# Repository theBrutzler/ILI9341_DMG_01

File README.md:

# ILI9341_DMG_01
 GESP Mainboard for ORIGINAL GAMEBOY

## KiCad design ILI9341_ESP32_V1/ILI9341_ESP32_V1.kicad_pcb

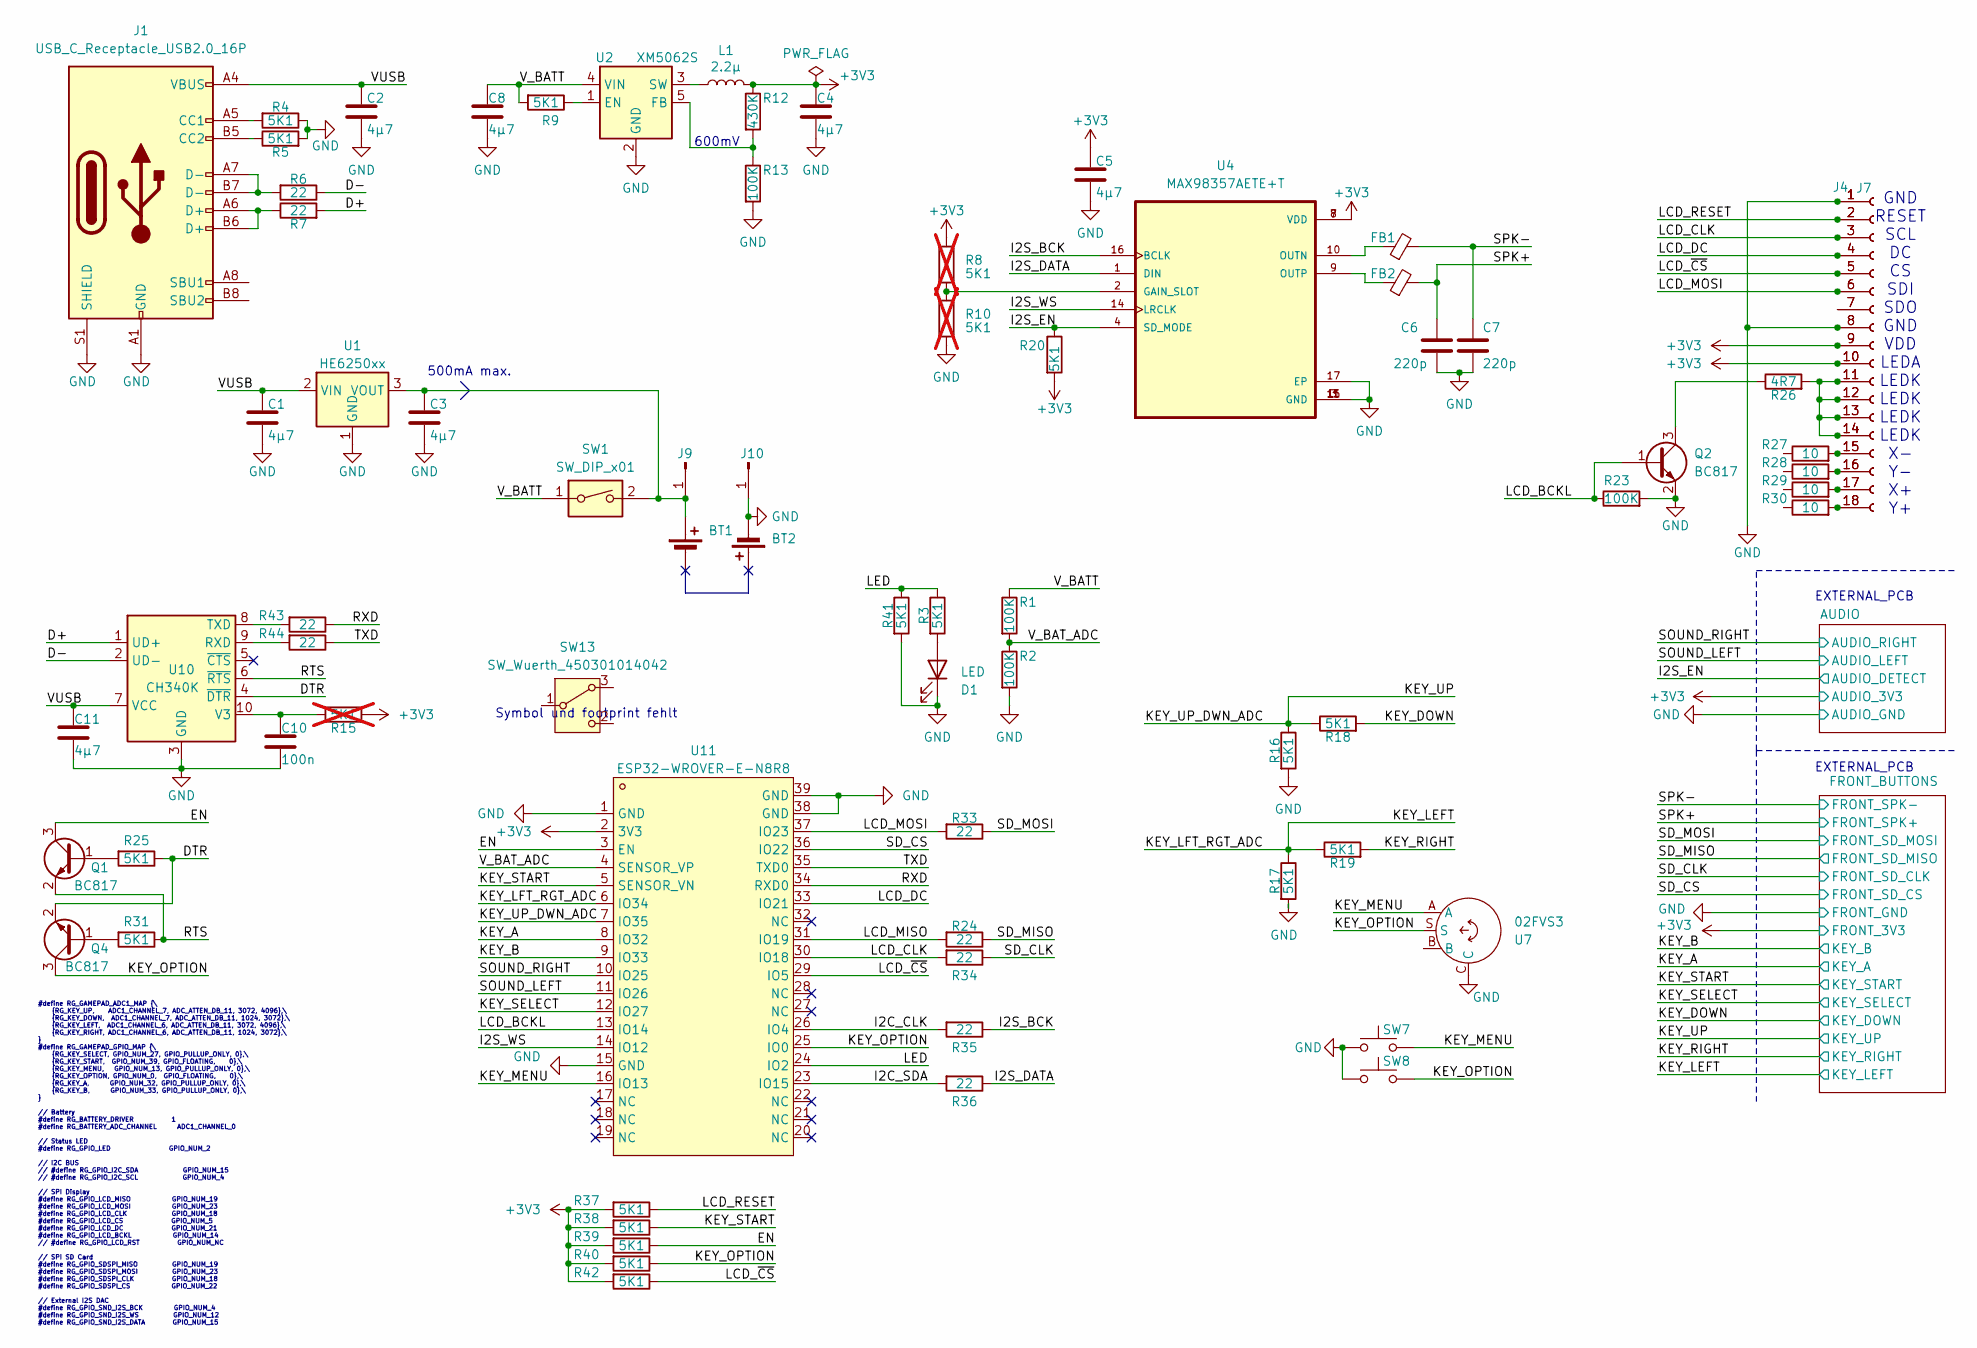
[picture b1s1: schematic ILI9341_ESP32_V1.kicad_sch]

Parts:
BT1: Battery_Cell; BATTERY_AA_SMD_PLUS; LCSC C964874
BT2: Battery_Cell; BATTERY_AA_SMD_MINUS; LCSC C964876
C1, C2, C3, C4, C5, C8, C11: 4µ7; C_1206_3216Metric
C6, C7: 220p; C_0603_1608Metric
C10: 100n; C_1206_3216Metric
D1: LED; LED_0603_1608Metric
FB1, FB2: FerriteBead_Small; L_0805_2012Metric
J1: USB_C_Receptacle_USB2.0_16P; USB_C_Receptacle_HRO_TYPE-C-31-M-12
J4, J7: Conn_01x18_Socket; solder connector 0.8mm 18 pin
J9: Conn_01x01_Pin; NINTENDO_PLUS
J10: Conn_01x01_Pin; NINTENDO_MINUS
L1: 2.2µ; L_1210_3225Metric_Pad1.42x2.65mm_HandSolder
Q1, Q2, Q4: BC817; SOT-23
R1, R2, R13, R23: 100K; R_0603_1608Metric_Pad0.98x0.95mm_HandSolder
R3, R4, R5, R9, R16, R17, R18, R19, R25, R31, R37, R38, R39, R40, R41, R42: 5K1; R_0603_1608Metric_Pad0.98x0.95mm_HandSolder
R6, R7, R24, R33, R34, R35, R36, R43, R44: 22; R_0603_1608Metric_Pad0.98x0.95mm_HandSolder
R8, R10: 5K1; R_0603_1608Metric; LCSC C26000; not fitted
R12: 430K; R_0603_1608Metric_Pad0.98x0.95mm_HandSolder
R15: 5K1; R_0603_1608Metric_Pad0.98x0.95mm_HandSolder; not fitted
R20: 5K1; R_0603_1608Metric; LCSC C26000
R26: 4R7; R_0603_1608Metric_Pad0.98x0.95mm_HandSolder
R27, R28, R29, R30: 10; R_0603_1608Metric_Pad0.98x0.95mm_HandSolder
SW1: SW_DIP_x01; SW_SPDT_PCM12; LCSC C3036445 C223846
SW7, SW8: SW_Push; RubberpadButton_250µ_250µ
SW13: SW_Wuerth_450301014042; SW_Slide-03_Wuerth-WS-SLTV_10x2.5x6.4_P2.54mm; LCSC C2939282
U1: HE6250xx; SOT-89-3; LCSC C711940
U2: XM5062S; SOT-23-5; LCSC C2924930
U4: MAX98357AETE+T; QFN-16-1EP_3x3mm_P0.5mm_EP1.45x1.45mm; LCSC C910544
U7: 02FVS3; LCSC C2925423
U10: CH340K; SSOP-10_3.9x4.9mm_P1.00mm_EP_3mmx2mm; LCSC C968586
U11: ESP32-WROVER-E-N8R8; WIFI-SMD_ESP32-WROVER-IE8MB; LCSC Part C2973667

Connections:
+3V3: C4.1, C5.1, J4.9, J4.10, J7.9, J7.10, L1.2, R8.1, R12.1, R15.2, R20.2, R37.2, R38.2, R39.2, R40.2, R42.2, U4.7 (VDD), U4.8 (VDD), U11.2 (3V3); also elsewhere on the board
/D+: R7.2, U10.1 (UD+)
/D-: R6.1, U10.2 (UD-)
/DTR: Q4.2 (E), R25.1, U10.4 (~DTR)
/EN: Q1.3 (C), R39.1, U11.3 (EN)
/I2C_CLK: R35.2, U11.26 (IO4)
/I2C_SDA: R36.2, U11.23 (IO15)
/I2S_BCK: R35.1, U4.16 (BCLK)
/I2S_DATA: R36.1, U4.1 (DIN)
/I2S_EN: R20.1, U4.4 (SD_MODE); also elsewhere on the board
/I2S_WS: U4.14 (LRCLK), U11.14 (IO12)
/KEY_A: U11.8 (IO32); also elsewhere on the board
/KEY_B: U11.9 (IO33); also elsewhere on the board
/KEY_DOWN: R18.2; also elsewhere on the board
/KEY_LEFT: R17.1, R19.1, U11.6 (IO34); also elsewhere on the board
/KEY_MENU: SW7.2, U7.A, U11.16 (IO13)
/KEY_OPTION: Q4.3 (C), R40.1, SW8.2, U7.S, U11.25 (IO0)
/KEY_RIGHT: R19.2; also elsewhere on the board
/KEY_SELECT: U11.12 (IO27); also elsewhere on the board
/KEY_START: R38.1, U11.5 (SENSOR_VN); also elsewhere on the board
/KEY_UP: R16.1, R18.1, U11.7 (IO35); also elsewhere on the board
/LCD_BCKL: Q2.1 (B), R23.1, U11.13 (IO14)
/LCD_CLK: J4.3, J7.3, R34.2, U11.30 (IO18); also elsewhere on the board
/LCD_DC: J4.4, J7.4, U11.33 (IO21); also elsewhere on the board
/LCD_MISO: R24.2, U11.31 (IO19)
/LCD_MOSI: J4.6, J7.6, R33.2, U11.37 (IO23); also elsewhere on the board
/LCD_RESET: J4.2, J7.2, R37.1; also elsewhere on the board
/LCD_~CS: J4.5, J7.5, R42.1, U11.29 (IO5); also elsewhere on the board
/LED: R3.1, R41.1, U11.24 (IO2)
/RTS: Q1.2 (E), R31.1, U10.6 (~RTS)
/RXD: R43.1, U11.34 (RXD0)
/SD_CLK: R34.1; also elsewhere on the board
/SD_CS: U11.36 (IO22); also elsewhere on the board
/SD_MISO: R24.1; also elsewhere on the board
/SD_MOSI: R33.1; also elsewhere on the board
/SOUND_LEFT: U11.11 (IO26); also elsewhere on the board
/SOUND_RIGHT: U11.10 (IO25); also elsewhere on the board
/SPK+: C6.1, FB2.2; also elsewhere on the board
/SPK-: C7.2, FB1.2; also elsewhere on the board
/TXD: R44.1, U11.35 (TXD0)
/VUSB: C1.1, C2.1, C11.1, J1.A4 (VBUS), J1.A9 (VBUS), J1.B4 (VBUS), J1.B9 (VBUS), U1.2 (VIN), U10.7 (VCC)
/V_BATT: C8.1, R1.1, R9.2, SW1.1, U2.4 (VIN)
/V_BAT_ADC: R1.2, R2.1, U11.4 (SENSOR_VP)
GND: BT2.2 (-), C1.2, C2.2, C3.2, C4.2, C5.2, C6.2, C7.1, C8.2, C10.2, C11.2, D1.1 (K), J1.A1 (GND), J1.A12 (GND), J1.B1 (GND), J1.B12 (GND), J1.S1 (SHIELD), J4.1, J4.8, J7.1, J7.8, J10.1, Q2.2 (E), R2.2, R4.1, R5.2, R10.2, R13.2, R16.2, R17.2, R23.2, R41.2, SW7.1, SW8.1, U1.1 (GND), U2.2 (GND), U4.3 (GND), U4.11 (GND), U4.15 (GND), U4.17 (EP), U7.C, U10.3 (GND), U10.PAD (GND), U11.1 (GND), U11.15 (GND), U11.38 (GND), U11.39 (GND); also elsewhere on the board
unnamed: BT1.1 (+), C3.1, J9.1, SW1.2, U1.3 (VOUT)
unnamed: D1.2 (A), R3.2
unnamed: J1.A5 (CC1), R4.2
unnamed: J1.B5 (CC2), R5.1
unnamed: J1.A6 (D+), J1.B6 (D+), R7.1
unnamed: J1.A7 (D-), J1.B7 (D-), R6.2
unnamed 70: J4.7, J7.7; also elsewhere on the board
unnamed 72: J4.11, J4.12, J4.13, J4.14, J7.11, J7.12, J7.13, J7.14, R26.2; also elsewhere on the board
unnamed 73: J4.15, J7.15, R27.2; also elsewhere on the board
unnamed 74: J4.16, J7.16, R28.2; also elsewhere on the board
unnamed 75: J4.17, J7.17, R29.2; also elsewhere on the board
unnamed 76: J4.18, J7.18, R30.2; also elsewhere on the board
unnamed: Q1.1 (B), R25.2
unnamed: Q2.3 (C), R26.1
unnamed: Q4.1 (B), R31.2
unnamed: R9.1, U2.1 (EN)
unnamed: R12.2, R13.1, U2.5 (FB)
unnamed: L1.1, U2.3 (SW)
unnamed: R8.2, R10.1, U4.2 (GAIN_SLOT)
unnamed: FB1.1, U4.10 (OUTN)
unnamed: FB2.1, U4.9 (OUTP)
unnamed: R44.2, U10.9 (RXD)
unnamed: R43.2, U10.8 (TXD)
unnamed: C10.1, R15.1, U10.10 (V3)

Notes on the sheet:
600mV
EXTERNAL_PCB
#define RG_GAMEPAD_ADC1_MAP {\ {RG_KEY_UP, ADC1_CHANNEL_7, ADC_ATTEN_DB_11, 3072, 4096},\ {RG_KEY_DOWN, ADC1_CHANNEL_7, ADC_ATTEN_DB_11, 1024, 3072},\ {RG_KEY_LEFT, ADC1_CHANNEL_6, ADC_ATTEN_DB_11, 3072, 4096},\ {RG_KEY_RIGHT, ADC1_CHANNEL_6, ADC_ATTEN_DB_11, 1024, 3072},\ } #define RG_GAMEPAD_GPIO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
500mA max.
Symbol und footprint fehlt
GND RESET SCL DC CS SDI SDO GND VDD LEDA LEDK LEDK LEDK LEDK X- Y- X+ Y+

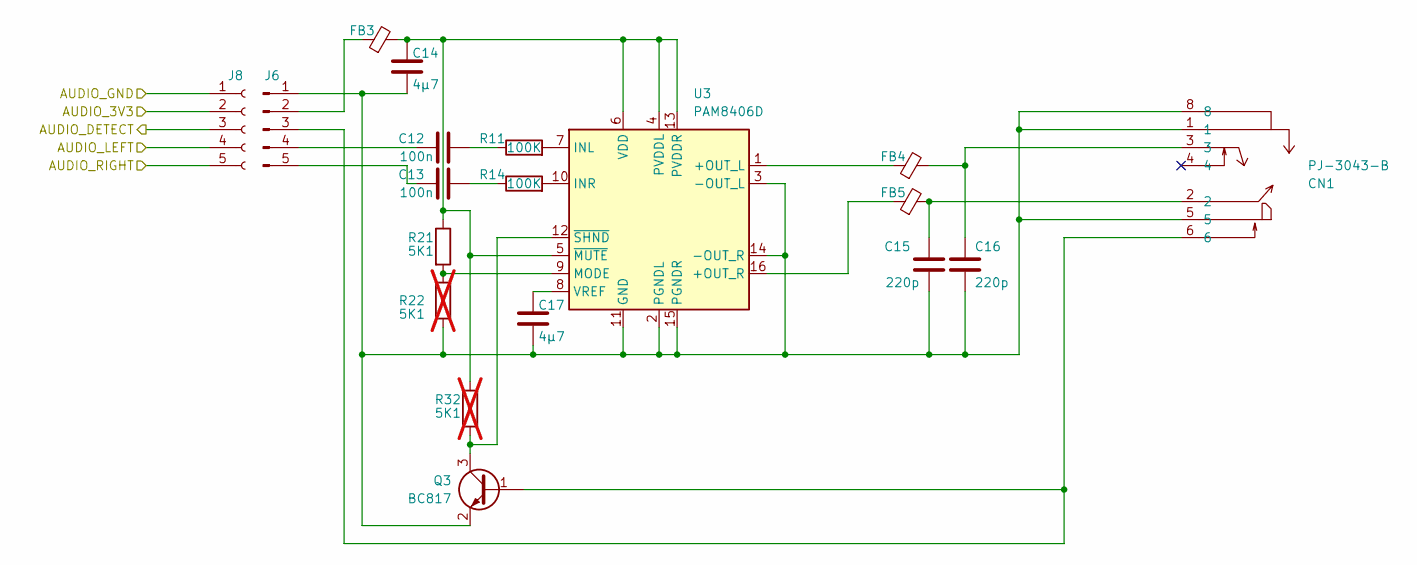
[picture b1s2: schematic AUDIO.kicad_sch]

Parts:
C12, C13: 100n; C_1206_3216Metric
C14, C17: 4µ7; C_1206_3216Metric
C15, C16: 220p; C_0603_1608Metric
CN1: PJ-3043-B; AUDIO-TH_PJ-3043-B; LCSC Part C2682182
FB3, FB4, FB5: FerriteBead_Small; L_0805_2012Metric
J6: Conn_01x05_Pin; PinHeader_1x05_P2.00mm_Vertical
J8: Conn_01x05_Socket; PinHeader_1x05_P2.00mm_Vertical
Q3: BC817; SOT-23
R11, R14: 100K; R_0603_1608Metric_Pad0.98x0.95mm_HandSolder
R21: 5K1; R_0603_1608Metric; LCSC C26000
R22, R32: 5K1; R_0603_1608Metric; LCSC C26000; not fitted
U3: PAM8406D; SOP-16_3.9x9.9mm_P1.27mm; LCSC C86270

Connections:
+3V3: J8.2; also elsewhere on the board
/I2S_EN: J8.3; also elsewhere on the board
/SOUND_LEFT: J8.4; also elsewhere on the board
/SOUND_RIGHT: J8.5; also elsewhere on the board
GND: J8.1; also elsewhere on the board
unnamed: C12.2, R11.1
unnamed: C13.2, R14.1
unnamed: C15.1, CN1.2, FB5.2
unnamed: C16.2, CN1.3, FB4.2
unnamed: C14.2, C15.2, C16.1, C17.2, CN1.1, CN1.5, CN1.8, J6.1, Q3.2 (E), R22.2, U3.2 (PGNDL), U3.3 (-OUT_L), U3.11 (GND), U3.14 (-OUT_R), U3.15 (PGNDR)
unnamed: FB3.1, J6.2
unnamed: CN1.6, J6.3, Q3.1 (B)
unnamed: C12.1, J6.4
unnamed: C13.1, J6.5
unnamed: Q3.3 (C), R32.2, U3.12 (~SHND)
unnamed: FB4.1, U3.1 (+OUT_L)
unnamed: FB5.1, U3.16 (+OUT_R)
unnamed: R11.2, U3.7 (INL)
unnamed: R14.2, U3.10 (INR)
unnamed: R21.2, R22.1, U3.9 (MODE)
unnamed: C14.1, FB3.2, R21.1, R32.1, U3.4 (PVDDL), U3.5 (~MUTE), U3.6 (VDD), U3.13 (PVDDR)
unnamed: C17.1, U3.8 (VREF)

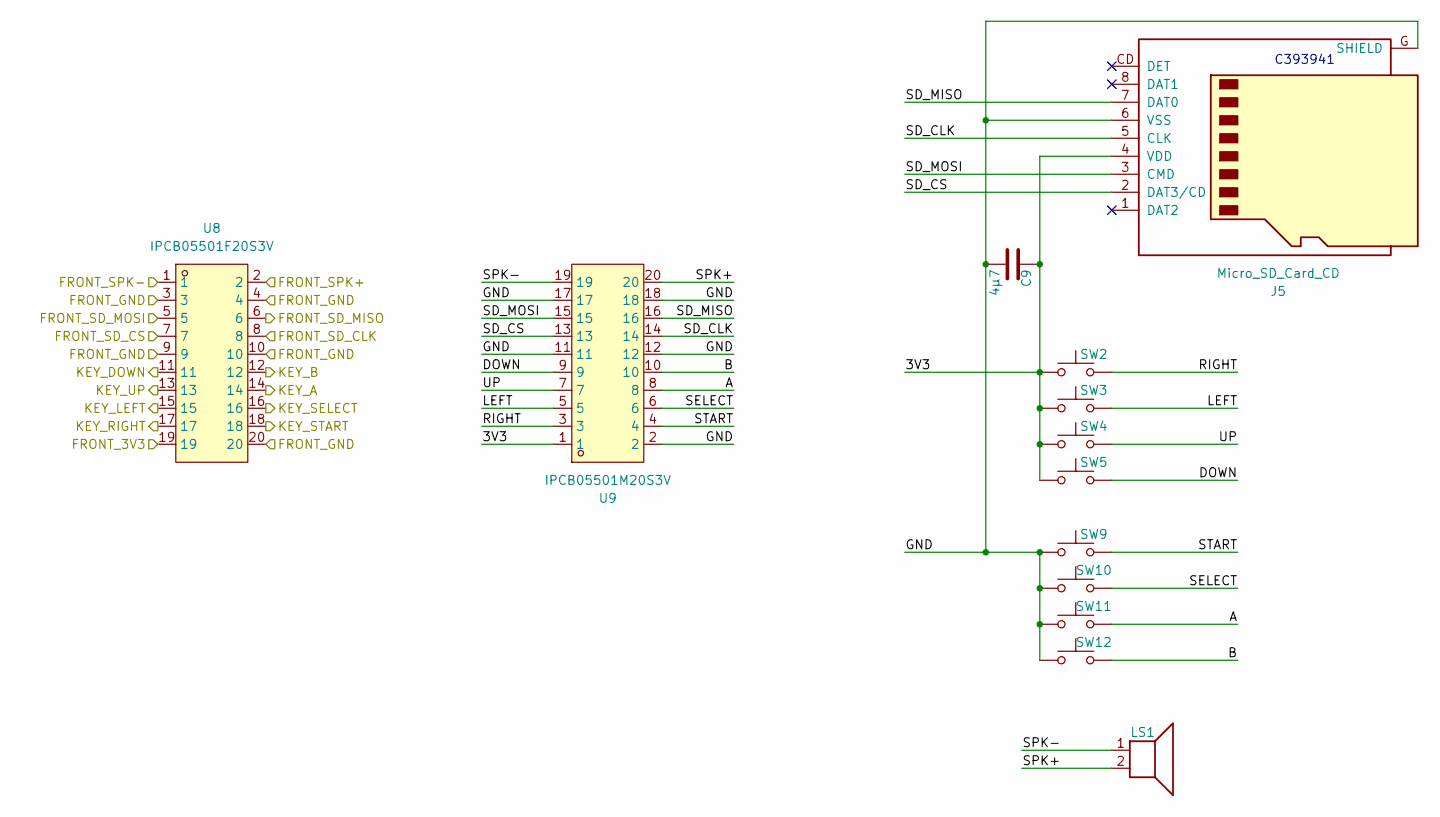
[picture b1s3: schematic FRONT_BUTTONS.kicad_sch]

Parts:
C9: 4µ7; C_1206_3216Metric
J5: Micro_SD_Card_CD; MicroSD_Self_ bomb; LCSC C393941
LS1: Speaker; PinHeader_1x02_P2.54mm_Vertical; LCSC C391015
SW2, SW3, SW4, SW5, SW9, SW10, SW11, SW12: SW_Push; RubberpadButton_250µ_250µ
U8: IPCB05501F20S3V; CONN-SMD_20P-P0.50_INCP_IPCB05501F20S3V; LCSC Part C5290330
U9: IPCB05501M20S3V; CONN-SMD_20P-P0.50_INCP_IPCB05501M20S3V; LCSC Part C5290329

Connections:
+3V3: U8.19; also elsewhere on the board
/FRONT_BUTTONS/3V3: C9.1, J5.4 (VDD), SW2.1, SW3.1, SW4.1, SW5.1, U9.1
/FRONT_BUTTONS/A: SW11.2, U9.8
/FRONT_BUTTONS/B: SW12.2, U9.10
/FRONT_BUTTONS/DOWN: SW5.2, U9.9
/FRONT_BUTTONS/GND: C9.2, J5.6 (VSS), J5.G (SHIELD), SW9.1, SW10.1, SW11.1, SW12.1, U9.2, U9.11, U9.12, U9.17, U9.18
/FRONT_BUTTONS/LEFT: SW3.2, U9.5
/FRONT_BUTTONS/RIGHT: SW2.2, U9.3
/FRONT_BUTTONS/SD_CLK: J5.5 (CLK), U9.14
/FRONT_BUTTONS/SD_CS: J5.2 (DAT3/CD), U9.13
/FRONT_BUTTONS/SD_MISO: J5.7 (DAT0), U9.16
/FRONT_BUTTONS/SD_MOSI: J5.3 (CMD), U9.15
/FRONT_BUTTONS/SELECT: SW10.2, U9.6
/FRONT_BUTTONS/SPK+: LS1.2, U9.20
/FRONT_BUTTONS/SPK-: LS1.1, U9.19
/FRONT_BUTTONS/START: SW9.2, U9.4
/FRONT_BUTTONS/UP: SW4.2, U9.7
/KEY_A: U8.14; also elsewhere on the board
/KEY_B: U8.12; also elsewhere on the board
/KEY_DOWN: U8.11; also elsewhere on the board
/KEY_LEFT: U8.15; also elsewhere on the board
/KEY_RIGHT: U8.17; also elsewhere on the board
/KEY_SELECT: U8.16; also elsewhere on the board
/KEY_START: U8.18; also elsewhere on the board
/KEY_UP: U8.13; also elsewhere on the board
/SD_CLK: U8.8; also elsewhere on the board
/SD_CS: U8.7; also elsewhere on the board
/SD_MISO: U8.6; also elsewhere on the board
/SD_MOSI: U8.5; also elsewhere on the board
/SPK+: U8.2; also elsewhere on the board
/SPK-: U8.1; also elsewhere on the board
GND: U8.3, U8.4, U8.9, U8.10, U8.20; also elsewhere on the board

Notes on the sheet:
C393941

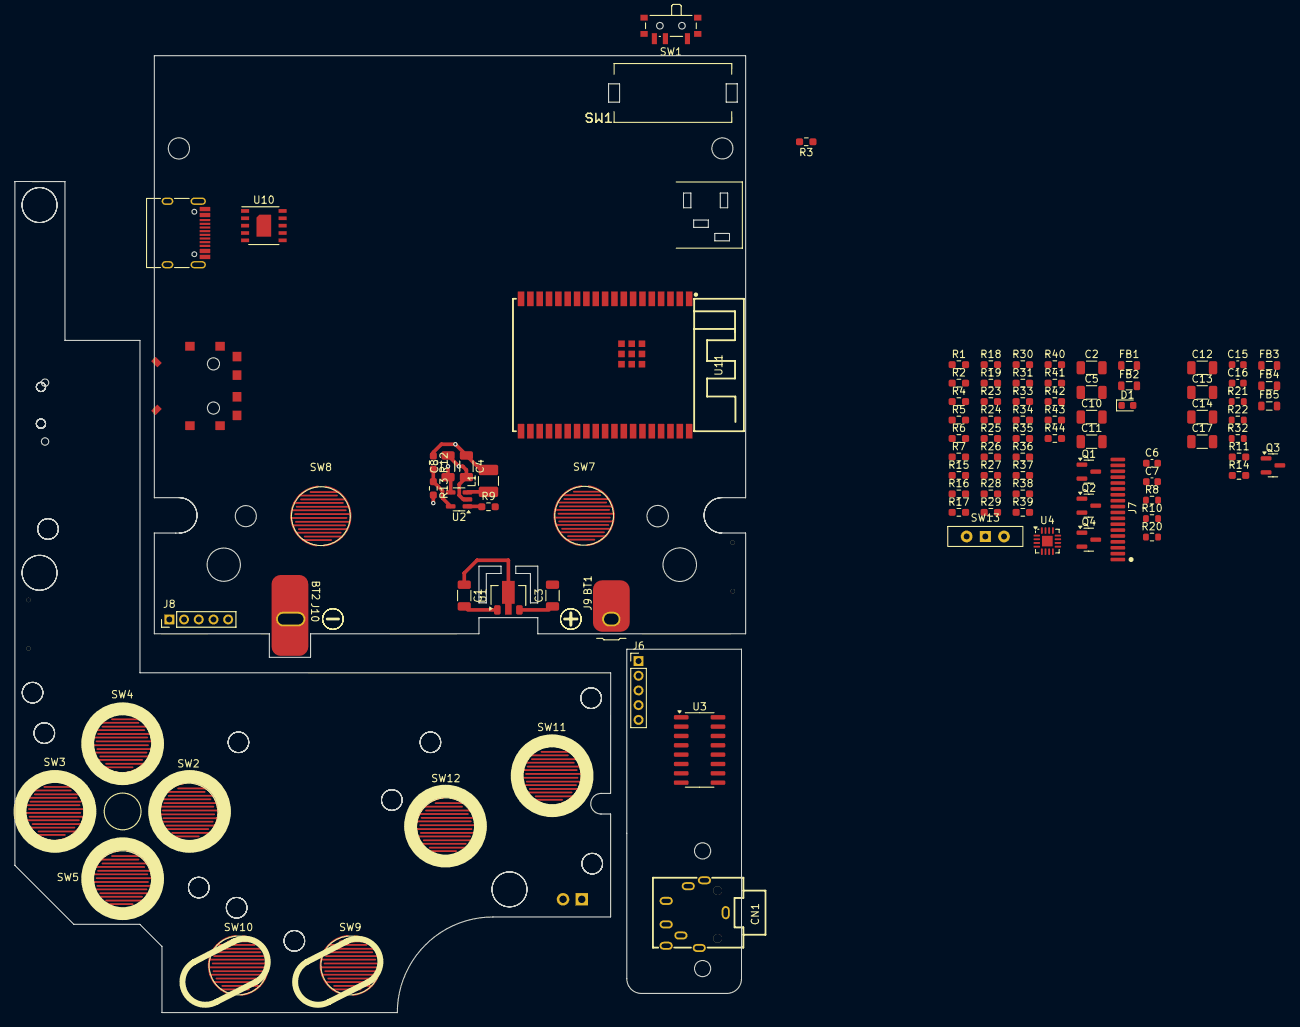
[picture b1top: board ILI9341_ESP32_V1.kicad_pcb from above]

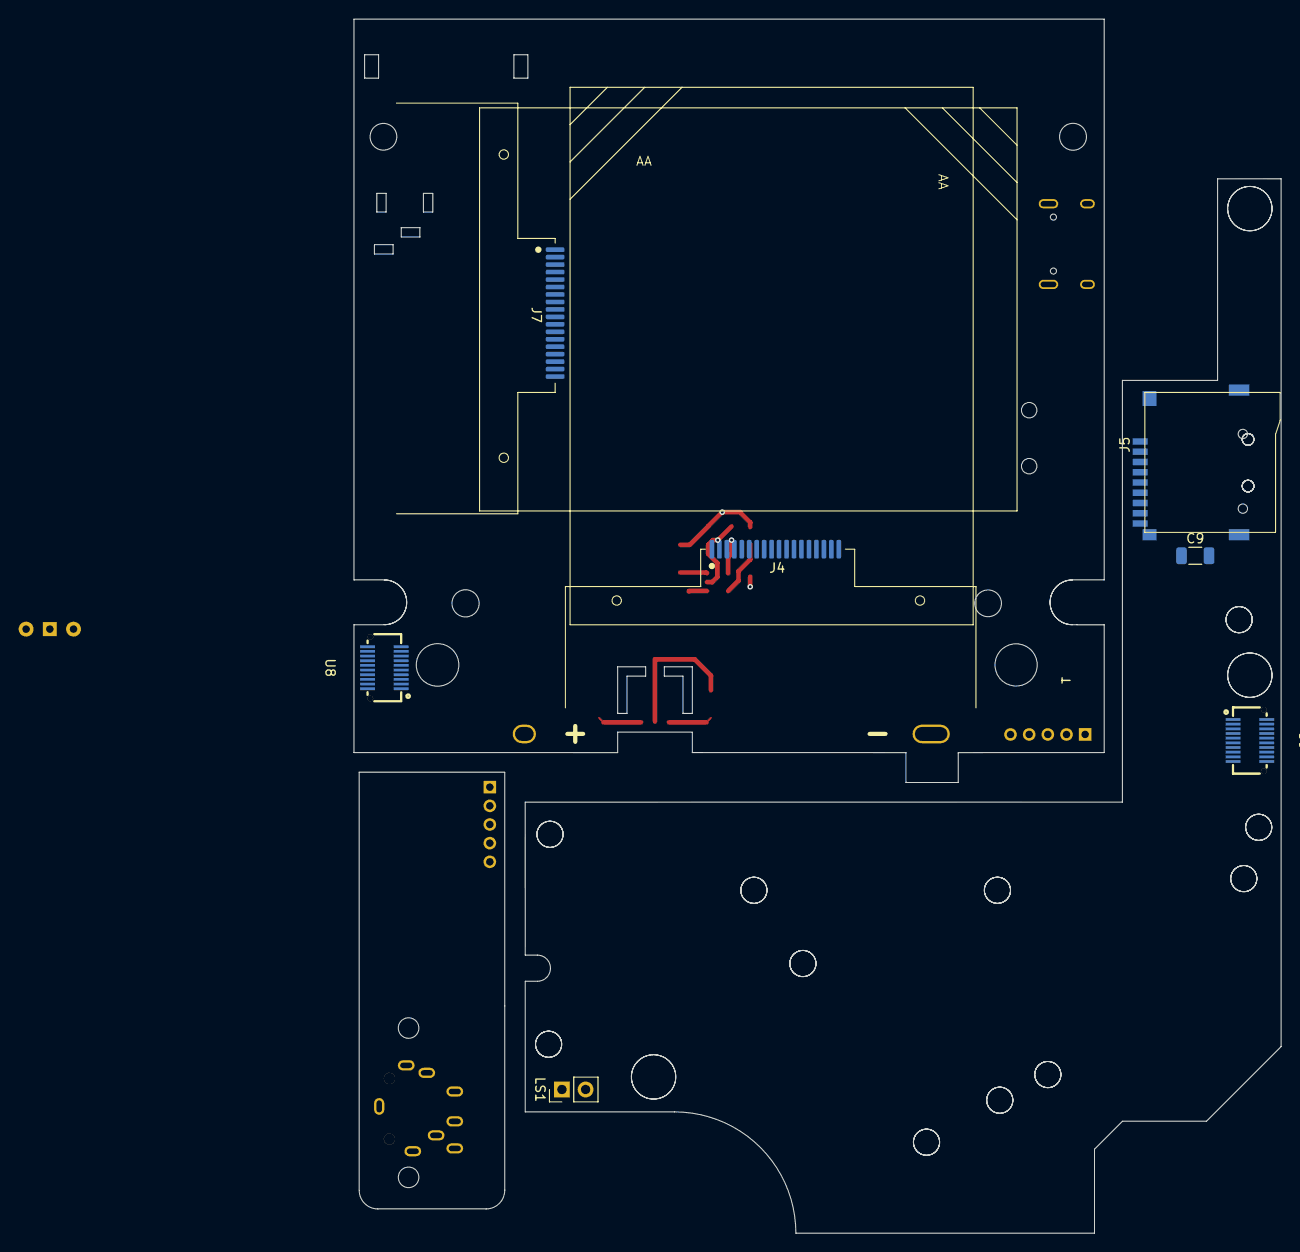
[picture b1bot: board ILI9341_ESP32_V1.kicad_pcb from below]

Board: 2 copper layers, 99.4 x 130.1 mm, 108 parts (7 on the bottom side), 101 nets.

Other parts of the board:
H1, H2: MountingHole; MountingHole_2.2mm_M2
J7#2: Conn_01x18_Socket; solder connector 0.8mm 18 pin

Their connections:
+3V3: J7#2.9; also elsewhere on the board
/LCD_CLK: J7#2.3; also elsewhere on the board
/LCD_DC: J7#2.4; also elsewhere on the board
/LCD_MOSI: J7#2.6; also elsewhere on the board
/LCD_RESET: J7#2.2; also elsewhere on the board
/LCD_~CS: J7#2.5; also elsewhere on the board
GND: J7#2.1, J7#2.8; also elsewhere on the board
unnamed 70: J7#2.7; also elsewhere on the board
unnamed 72: J7#2.11, J7#2.12, J7#2.13, J7#2.14; also elsewhere on the board
unnamed 73: J7#2.15; also elsewhere on the board
unnamed 74: J7#2.16; also elsewhere on the board
unnamed 75: J7#2.17; also elsewhere on the board
unnamed 76: J7#2.18; also elsewhere on the board

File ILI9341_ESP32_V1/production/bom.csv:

Designator,Footprint,Quantity,Value,LCSC Part #
BT1,BATTERY_AA_SMD_PLUS,1,Battery_Cell,C964874
BT2,BATTERY_AA_SMD_MINUS,1,Battery_Cell,C964876
"C1, C11, C12, C15, C18, C19, C2, C3, C4, C5, C8, C9",1206,12,4µ7,
"C10, C13, C14",1206,3,100n,
"C16, C17, C6, C7",0603,4,220p,
CN1,AUDIO-TH_PJ-3043-B,1,PJ-3043-B,C2682182
D1,0603,1,LED,
"D2, D3",Nexperia_CFP3_SOD-123W,2,D,
DC1,DC-IN-TH_DC-011A,1,DC-011A,C480366
"FB1, FB2, FB3, FB4, FB5, FB6, FB7, FB9",0805,8,FerriteBead_Small,
J1,USB_C_Receptacle_HRO_TYPE-C-31-M-12,1,USB_C_Receptacle_USB2.0_16P,
J10,NINTENDO_MINUS,1,Conn_01x01_Pin,
J2,PinHeader_1x04_P2.00mm_Vertical,1,Conn_01x04_Pin,
J3,PinHeader_1x04_P2.00mm_Vertical,1,Conn_01x04_Socket,
"J4, J7",solder connector 0.8mm 18 pin,2,Conn_01x18_Socket,
J5,MicroSD_Self_ bomb,1,Micro_SD_Card_CD,C393941
J9,NINTENDO_PLUS,1,Conn_01x01_Pin,
L1,1210,1,2.2µ,
LS1,PinHeader_1x02_P2.54mm_Vertical,1,Speaker,C391015
"Q1, Q2, Q3, Q4",SOT-23,4,BC817,
"R1, R13, R2, R22, R23, R32",0603,6,100K,
"R11, R20, R21",0603,3,5K1,C26000
R12,0603,1,430K,
"R16, R17, R18, R19, R25, R3, R31, R37, R38, R39, R4, R40, R41, R42, R5, R9",0603,16,5K1,
"R24, R33, R34, R35, R36, R43, R44, R6, R7",0603,9,22,
R26,0603,1,4R7,
SW1,SW-TH_SS-12F23-G040,1,SS-12F23-G040,C2848932
"SW10, SW11, SW12, SW2, SW3, SW4, SW5, SW7, SW8, SW9",RubberpadButton_250µ_250µ,10,SW_Push,
U1,SOT-89-3,1,HE6250xx,C711940
U10,SSOP-10_3.9x4.9mm_P1.00mm_EP_3mmx2mm,1,CH340K,C968586
U11,WIFI-SMD_ESP32-WROVER-IE8MB,1,ESP32-WROVER-E-N8R8,C2973667
U2,SOT-23-5,1,XM5062S,C2924930
U3,SOP-16_3.9x9.9mm_P1.27mm,1,PAM8406D,C86270
U4,QFN-16-1EP_3x3mm_P0.5mm_EP1.45x1.45mm,1,MAX98357AETE+T,C910544
U7,02FVS3,1,02FVS3,C2925423
U8,CONN-SMD_20P-P0.50_INCP_IPCB05501F20S3V,1,IPCB05501F20S3V,C5290330
U9,CONN-SMD_20P-P0.50_INCP_IPCB05501M20S3V,1,IPCB05501M20S3V,C5290329

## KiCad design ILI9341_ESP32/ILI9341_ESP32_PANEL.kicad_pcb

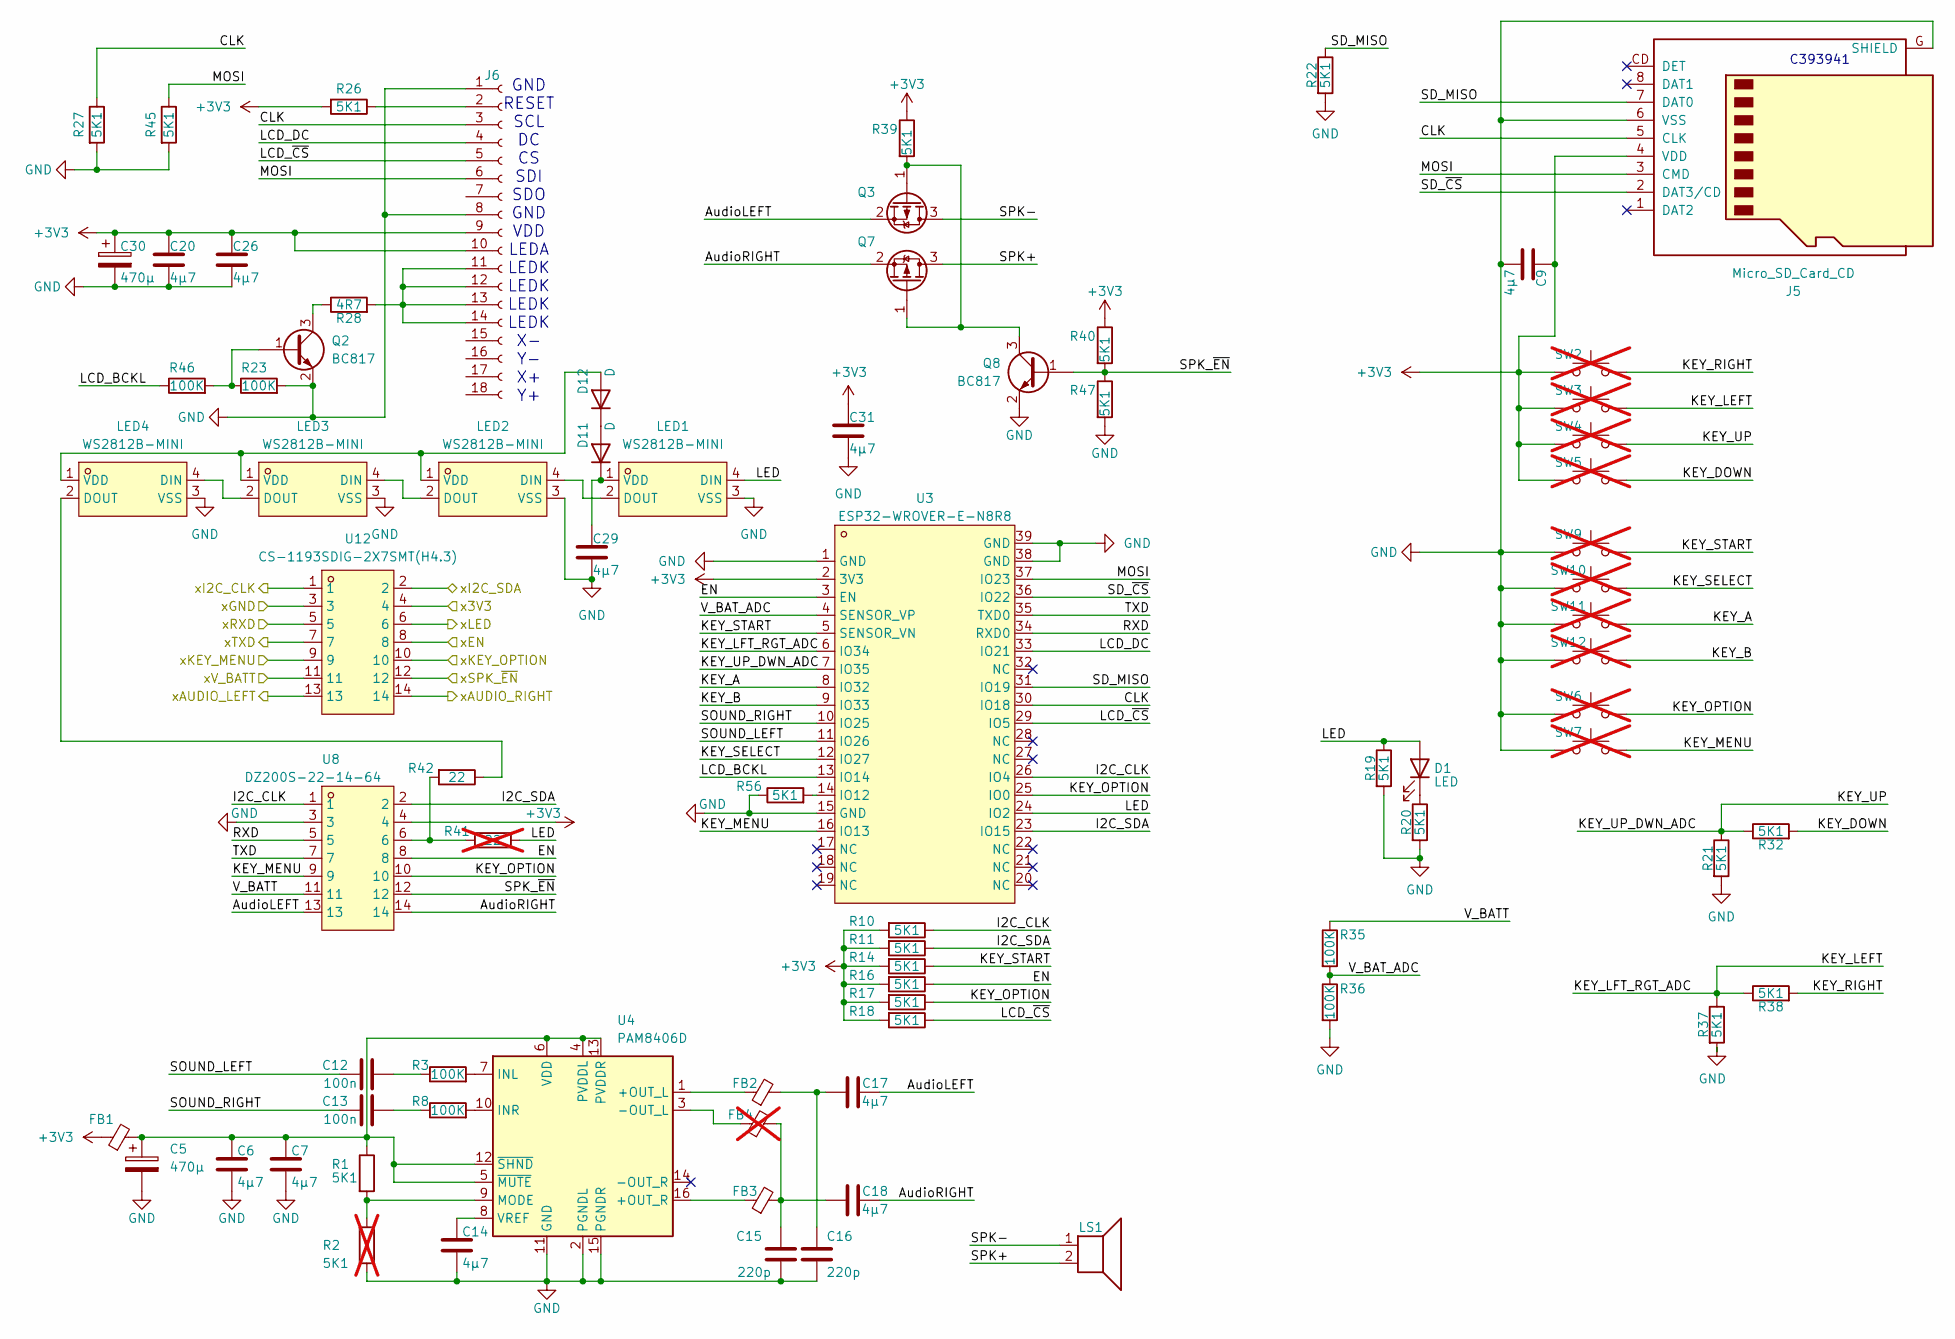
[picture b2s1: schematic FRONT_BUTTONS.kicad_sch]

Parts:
C5, C30: 470µ; CP_EIA-7343-43_Kemet-X; LCSC C724264
C6, C7, C9, C14, C17, C18, C20, C26, C29, C31: 4µ7; C_1206_3216Metric; LCSC C282809
C12, C13: 100n; C_0603_1608Metric
C15, C16: 220p; C_0603_1608Metric; LCSC C107081
D1: LED; LED_0603_1608Metric
D11, D12: D; Nexperia_CFP3_SOD-123W; LCSC C5120763
FB1, FB2, FB3: FerriteBead_Small; L_0805_2012Metric; LCSC C963878
FB4: FerriteBead_Small; L_0805_2012Metric; LCSC C963878; not fitted
J5: Micro_SD_Card_CD; MicroSD_Self_ bomb; LCSC C393941
J6: Conn_01x18_Socket; solder connector 0.8mm 18 pin
LED1, LED2, LED3, LED4: WS2812B-MINI; LED-SMD_4P-L3.5-W3.5-TL_WS2812B; LCSC C527089
LS1: Speaker; PinHeader_1x02_P2.54mm_Vertical; LCSC C391015
Q2, Q8: BC817; SOT-323_SC-70; LCSC C383187
Q3, Q7: PMOS; SOT-323_SC-70; LCSC C19078062
R1, R10, R11, R14, R16, R17, R18, R19, R20, R21, R22, R26, R27, R32, R37, R38, R39, R40, R45, R47, R56: 5K1; R_0603_1608Metric; LCSC C26000
R2: 5K1; R_0603_1608Metric; LCSC C26000; not fitted
R3, R8, R23, R35, R36, R46: 100K; R_0603_1608Metric; LCSC C15458
R28: 4R7; R_0603_1608Metric; LCSC C491192
R41: 22; R_0603_1608Metric; LCSC C1203; not fitted
R42: 22; R_0603_1608Metric; LCSC C1203
SW2, SW3, SW4, SW5, SW6, SW7, SW9, SW10, SW11, SW12: SW_Push; RubberpadButton_250µ_250µ; not fitted
U3: ESP32-WROVER-E-N8R8; WIFI-SMD_ESP32-WROVER-IE8MB; LCSC C2973667
U4: PAM8406D; SOP-16_3.9x9.9mm_P1.27mm; LCSC C86270
U8: DZ200S-22-14-64; HDR-SMD_14P-P2.00-V-M-R2-C7-LS6.4; LCSC C5160772
U12: CS-1193SDIG-2X7SMT(H4.3); PM200-2-07-S-4.3; LCSC C3975171

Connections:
+3V3: C9.1, C20.1, C26.1, C30.1, C31.1, FB1.1, J5.4 (VDD), J6.9, J6.10, R10.2, R11.2, R14.2, R16.2, R17.2, R18.2, R26.2, R39.1, R40.1, SW2.1, SW3.1, SW4.1, SW5.1, U3.2 (3V3), U8.4
/FRONT_BUTTONS/AudioLEFT: C17.2, Q3.2 (S), U8.13
/FRONT_BUTTONS/AudioRIGHT: C18.2, Q7.2 (S), U8.14
/FRONT_BUTTONS/CLK: J5.5 (CLK), J6.3, R27.1, U3.30 (IO18)
/FRONT_BUTTONS/EN: R16.1, U3.3 (EN), U8.8
/FRONT_BUTTONS/I2C_CLK: R10.1, U3.26 (IO4), U8.1
/FRONT_BUTTONS/I2C_SDA: R11.1, U3.23 (IO15), U8.2
/FRONT_BUTTONS/KEY_A: SW11.2, U3.8 (IO32)
/FRONT_BUTTONS/KEY_B: SW12.2, U3.9 (IO33)
/FRONT_BUTTONS/KEY_DOWN: R32.2, SW5.2
/FRONT_BUTTONS/KEY_LEFT: R37.1, R38.1, SW3.2, U3.6 (IO34)
/FRONT_BUTTONS/KEY_MENU: SW7.2, U3.16 (IO13), U8.9
/FRONT_BUTTONS/KEY_OPTION: R17.1, SW6.2, U3.25 (IO0), U8.10
/FRONT_BUTTONS/KEY_RIGHT: R38.2, SW2.2
/FRONT_BUTTONS/KEY_SELECT: SW10.2, U3.12 (IO27)
/FRONT_BUTTONS/KEY_START: R14.1, SW9.2, U3.5 (SENSOR_VN)
/FRONT_BUTTONS/KEY_UP: R21.1, R32.1, SW4.2, U3.7 (IO35)
/FRONT_BUTTONS/LCD_BCKL: R46.1, U3.13 (IO14)
/FRONT_BUTTONS/LCD_DC: J6.4, U3.33 (IO21)
/FRONT_BUTTONS/LCD_~CS: J6.5, R18.1, U3.29 (IO5)
/FRONT_BUTTONS/LED: D1.2 (A), LED1.4 (DIN), R19.1, R41.1, U3.24 (IO2)
/FRONT_BUTTONS/MOSI: J5.3 (CMD), J6.6, R45.1, U3.37 (IO23)
/FRONT_BUTTONS/RXD: U3.34 (RXD0), U8.5
/FRONT_BUTTONS/SD_MISO: J5.7 (DAT0), R22.1, U3.31 (IO19)
/FRONT_BUTTONS/SD_~CS: J5.2 (DAT3/CD), U3.36 (IO22)
/FRONT_BUTTONS/SOUND_LEFT: C12.1, U3.11 (IO26)
/FRONT_BUTTONS/SOUND_RIGHT: C13.1, U3.10 (IO25)
/FRONT_BUTTONS/SPK+: LS1.2, Q7.3 (D)
/FRONT_BUTTONS/SPK-: LS1.1, Q3.3 (D)
/FRONT_BUTTONS/SPK_~EN: Q8.1 (B), R40.2, R47.1, U8.12
/FRONT_BUTTONS/TXD: U3.35 (TXD0), U8.7
/FRONT_BUTTONS/V_BATT: R35.1, U8.11
/FRONT_BUTTONS/V_BAT_ADC: R35.2, R36.1, U3.4 (SENSOR_VP)
GND: C5.2, C6.2, C7.2, C9.2, C14.2, C15.2, C16.1, C20.2, C26.2, C29.2, C30.2, C31.2, J5.6 (VSS), J5.G (SHIELD), J6.1, J6.8, LED1.3 (VSS), LED2.3 (VSS), LED3.3 (VSS), LED4.3 (VSS), Q2.2 (E), Q8.2 (E), R2.2, R19.2, R20.2, R21.2, R22.2, R23.2, R27.2, R36.2, R37.2, R45.2, R47.2, R56.1, SW6.1, SW7.1, SW9.1, SW10.1, SW11.1, SW12.1, U3.1 (GND), U3.15 (GND), U3.38 (GND), U3.39 (GND), U4.2 (PGNDL), U4.11 (GND), U4.15 (PGNDR), U8.3
unnamed: C12.2, R3.1
unnamed: C13.2, R8.1
unnamed: C15.1, C18.1, FB3.2, FB4.2
unnamed: C16.2, C17.1, FB2.2
unnamed: D1.1 (K), R20.1
unnamed: D11.2 (A), D12.1 (K)
unnamed: C29.1, D11.1 (K), LED1.1 (VDD)
unnamed: D12.2 (A), LED2.1 (VDD), LED3.1 (VDD), LED4.1 (VDD)
unnamed: J6.2, R26.1
unnamed: J6.11, J6.12, J6.13, J6.14, R28.2
unnamed: LED1.2 (DOUT), LED2.4 (DIN)
unnamed: LED2.2 (DOUT), LED3.4 (DIN)
unnamed: LED3.2 (DOUT), LED4.4 (DIN)
unnamed: LED4.2 (DOUT), R42.1
unnamed: Q2.1 (B), R23.1, R46.2
unnamed: Q2.3 (C), R28.1
unnamed: Q3.1 (G), Q7.1 (G), Q8.3 (C), R39.2
unnamed: R41.2, R42.2, U8.6
unnamed: R56.2, U3.14 (IO12)
unnamed: FB2.1, U4.1 (+OUT_L)
unnamed: FB3.1, U4.16 (+OUT_R)
unnamed: FB4.1, U4.3 (-OUT_L)
unnamed: R3.2, U4.7 (INL)
unnamed: R8.2, U4.10 (INR)
unnamed: R1.2, R2.1, U4.9 (MODE)
unnamed: C5.1, C6.1, C7.1, FB1.2, R1.1, U4.4 (PVDDL), U4.5 (~MUTE), U4.6 (VDD), U4.12 (~SHND), U4.13 (PVDDR)
unnamed: C14.1, U4.8 (VREF)

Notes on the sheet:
GND RESET SCL DC CS SDI SDO GND VDD LEDA LEDK LEDK LEDK LEDK X- Y- X+ Y+
C393941

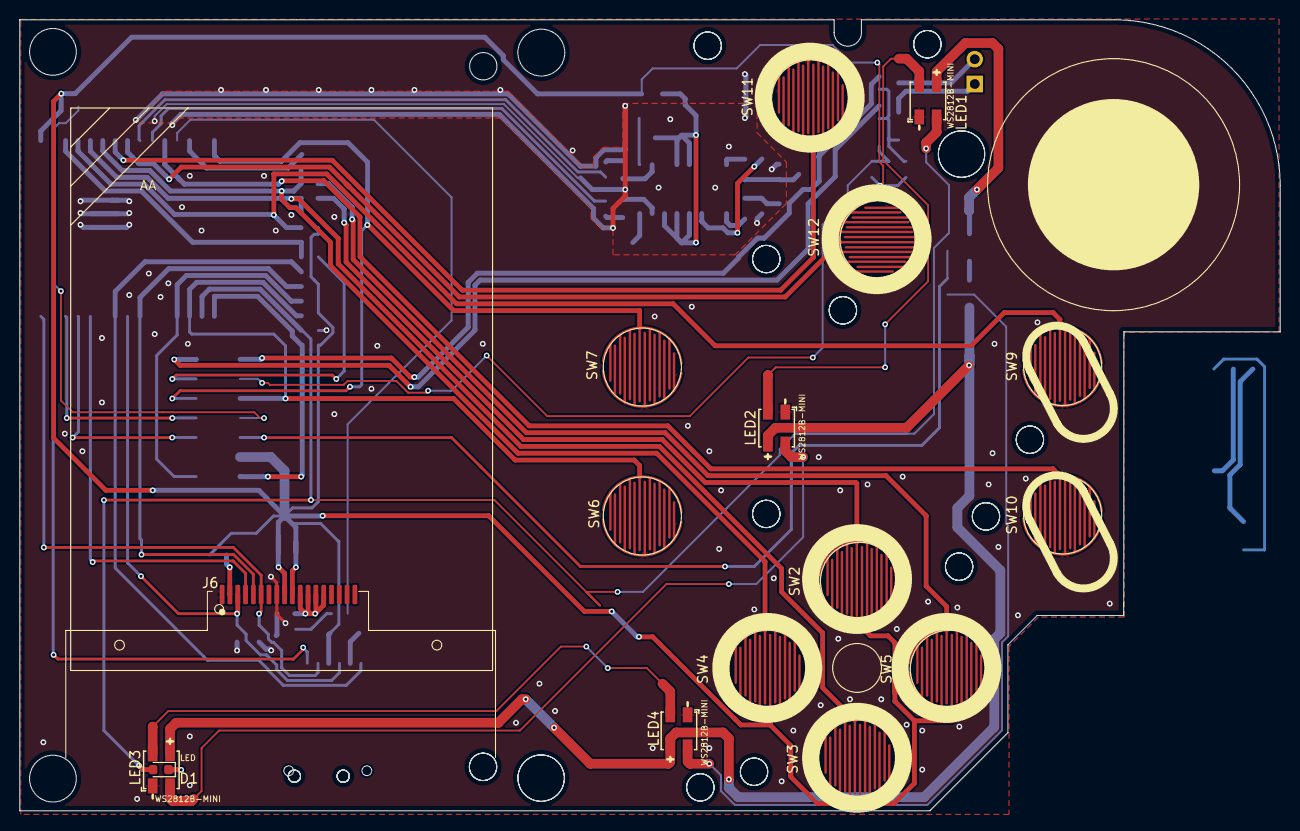
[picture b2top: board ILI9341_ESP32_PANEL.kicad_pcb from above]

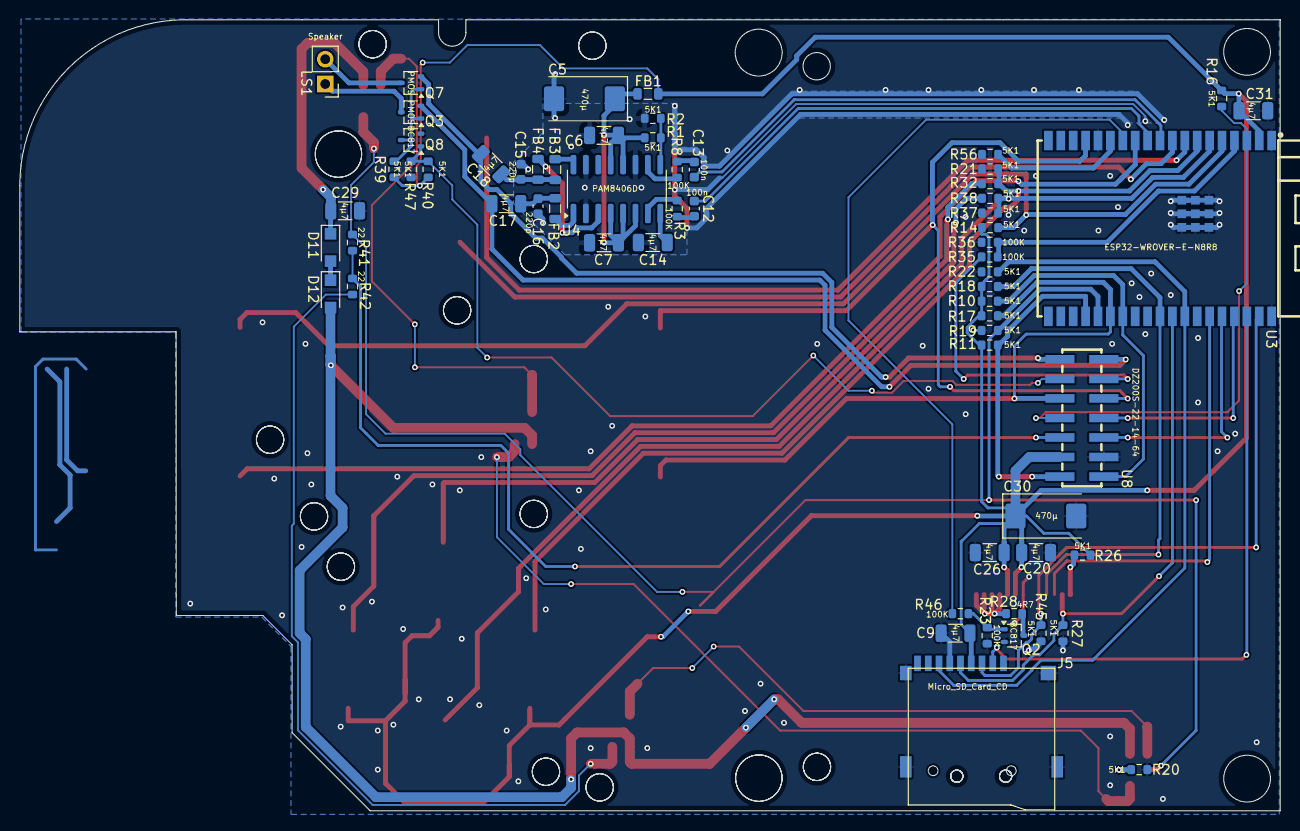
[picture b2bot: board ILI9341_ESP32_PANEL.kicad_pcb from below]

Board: 2 copper layers, 129.1 x 81.0 mm, 78 parts (62 on the bottom side), 61 nets.

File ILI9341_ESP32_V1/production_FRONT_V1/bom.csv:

Designator,Footprint,Quantity,Value,LCSC Part #
"C20, C9",1206,2,4µ7,
J5,MicroSD_Self_ bomb,1,Micro_SD_Card_CD,C393941
J6,solder connector 0.8mm 18 pin,1,Conn_01x18_Socket,
LS1,PinHeader_1x02_P2.54mm_Vertical,1,Speaker,C391015
Q2,SOT-323_SC-70,1,BC817,C383187
R23,0603,1,100K,
"R26, R27, R45",0603,3,5K1,
R28,0603,1,4R7,
SM3,Symbol_kurzschlussblog,1,SYM_Arrow45_Tiny,
"SW10, SW11, SW12, SW2, SW3, SW4, SW5, SW9",RubberpadButton_250µ_250µ,8,SW_Push,
U9,CONN-SMD_20P-P0.50_INCP_IPCB05501M20S3V,1,IPCB05501M20S3V,C5290329
